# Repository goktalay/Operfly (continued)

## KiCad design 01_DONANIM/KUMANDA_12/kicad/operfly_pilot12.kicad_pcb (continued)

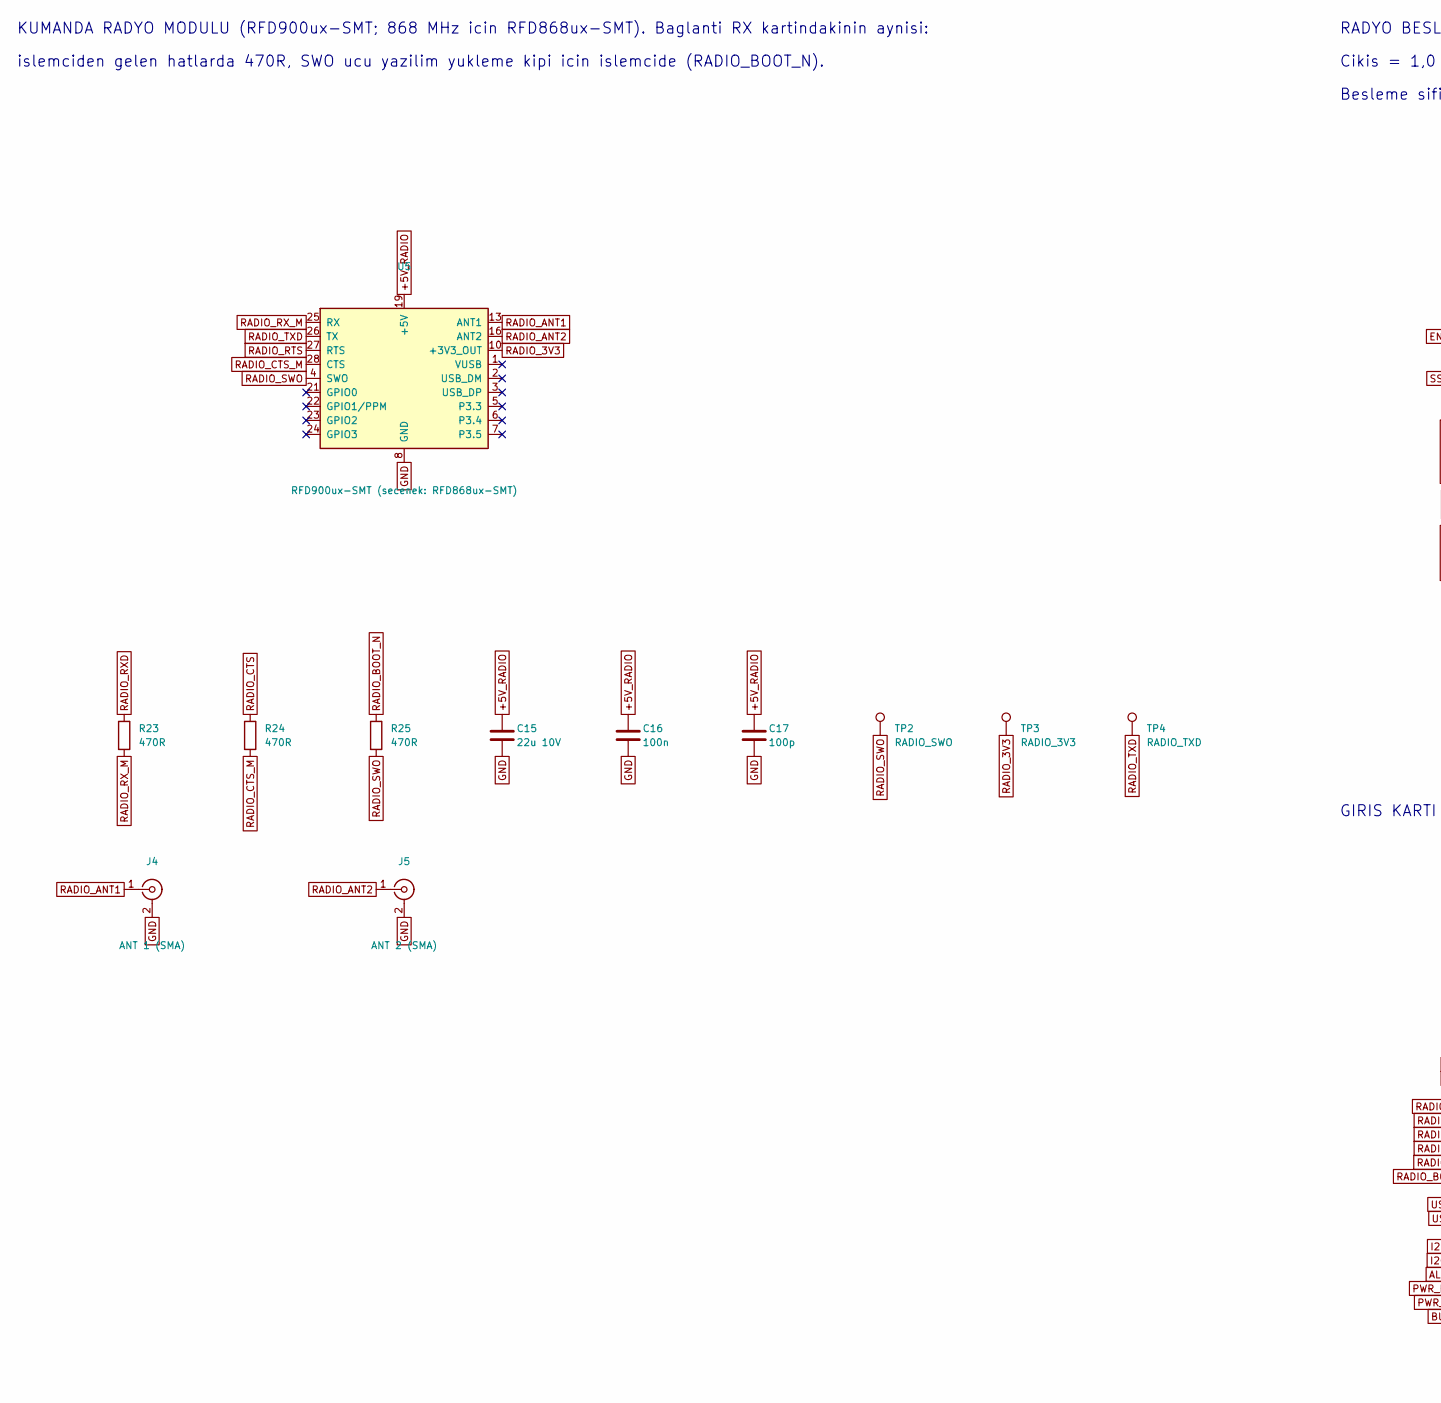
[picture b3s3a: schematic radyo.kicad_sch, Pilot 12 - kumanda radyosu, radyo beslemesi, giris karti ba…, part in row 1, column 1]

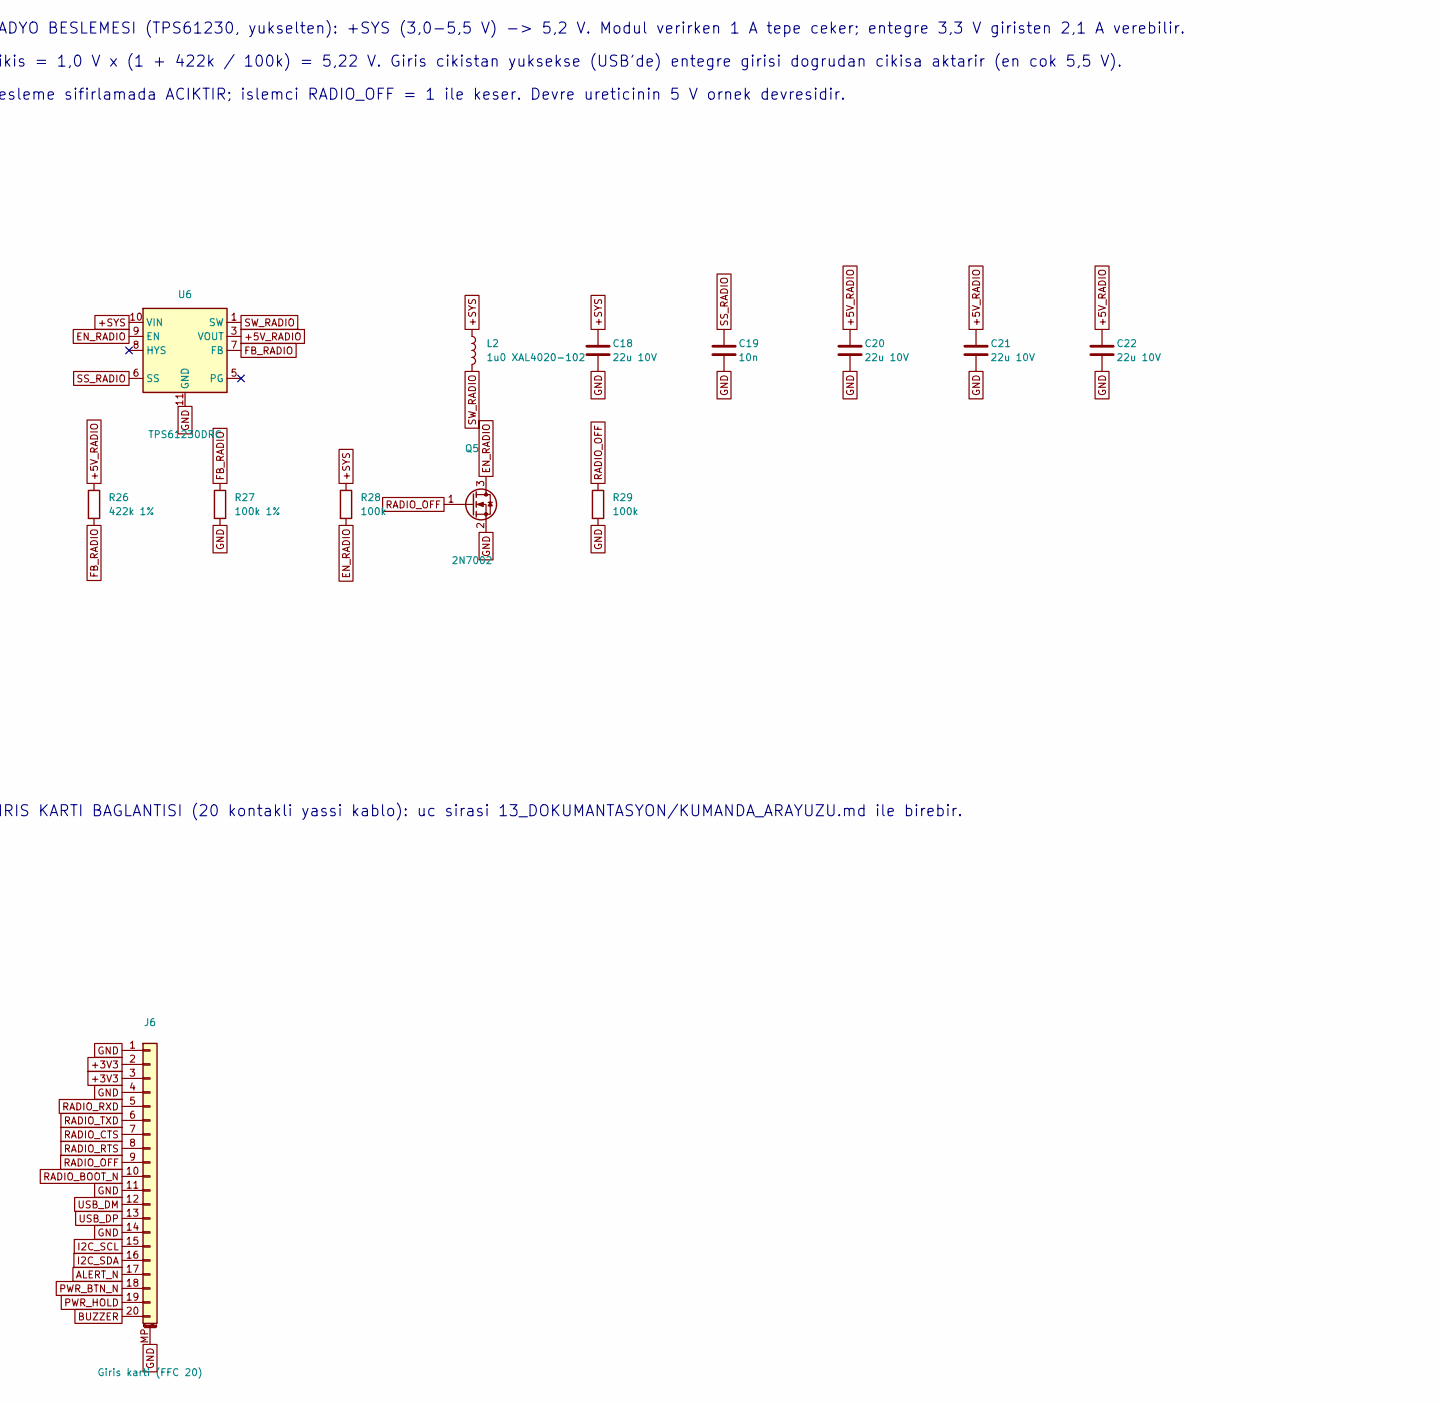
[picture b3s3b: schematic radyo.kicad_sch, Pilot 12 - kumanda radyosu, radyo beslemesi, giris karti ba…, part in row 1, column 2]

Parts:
C15, C18, C20, C21, C22: 22u 10V; C_1206_3216Metric
C16: 100n; C_0402_1005Metric
C17: 100p; C_0402_1005Metric
C19: 10n; C_0402_1005Metric
J4: ANT 1 (SMA); SMA_Amphenol_132289_EdgeMount
J5: ANT 2 (SMA); SMA_Amphenol_132289_EdgeMount
J6: Giris karti (FFC 20); Hirose_FH12-20S-0.5SH_1x20-1MP_P0.50mm_Horizontal
L2: 1u0 XAL4020-102; L_Coilcraft_XAL4020-XXX
Q5: 2N7002; SOT-23
R23, R24, R25: 470R; R_0402_1005Metric
R26: 422k 1%; R_0402_1005Metric
R27: 100k 1%; R_0402_1005Metric
R28, R29: 100k; R_0402_1005Metric
TP2: RADIO_SWO; TestPoint_Pad_D1.0mm
TP3: RADIO_3V3; TestPoint_Pad_D1.0mm
TP4: RADIO_TXD; TestPoint_Pad_D1.0mm
U5: RFD900ux-SMT (secenek: RFD868ux-SMT); RFDesign_RFD900ux-SMT
U6: TPS61230DRC; Texas_S-PVSON-N10_ThermalVias

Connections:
+3V3: J6.2, J6.3; also elsewhere on the board
+5V_RADIO: C15.1, C16.1, C17.1, C20.1, C21.1, C22.1, R26.1, U5.19 (+5V), U6.3 (VOUT), U6.4 (VOUT)
+SYS: C18.1, L2.1, R28.1, U6.10 (VIN); also elsewhere on the board
ALERT_N: J6.17; also elsewhere on the board
BUZZER: J6.20; also elsewhere on the board
EN_RADIO: Q5.3 (D), R28.2, U6.9 (EN)
FB_RADIO: R26.2, R27.1, U6.7 (FB)
GND: C15.2, C16.2, C17.2, C18.2, C19.2, C20.2, C21.2, C22.2, J4.2 (Ext), J5.2 (Ext), J6.1, J6.4, J6.11, J6.14, J6.MP (MountPin), Q5.2 (S), R27.2, R29.2, U5.8 (GND), U5.9 (GND), U5.11 (GND), U5.12 (GND), U5.14 (GND), U5.15 (GND), U5.17 (GND), U5.18 (GND), U5.20 (GND), U5.29 (GND), U5.30 (GND), U6.11 (GND); also elsewhere on the board
I2C_SCL: J6.15; also elsewhere on the board
I2C_SDA: J6.16; also elsewhere on the board
PWR_BTN_N: J6.18; also elsewhere on the board
PWR_HOLD: J6.19; also elsewhere on the board
RADIO_3V3: TP3.1, U5.10 (+3V3_OUT)
RADIO_ANT1: J4.1 (In), U5.13 (ANT1)
RADIO_ANT2: J5.1 (In), U5.16 (ANT2)
RADIO_BOOT_N: J6.10, R25.1
RADIO_CTS: J6.7, R24.1
RADIO_CTS_M: R24.2, U5.28 (CTS)
RADIO_OFF: J6.9, Q5.1 (G), R29.1
RADIO_RTS: J6.8, U5.27 (RTS)
RADIO_RXD: J6.5, R23.1
RADIO_RX_M: R23.2, U5.25 (RX)
RADIO_SWO: R25.2, TP2.1, U5.4 (SWO)
RADIO_TXD: J6.6, TP4.1, U5.26 (TX)
SS_RADIO: C19.1, U6.6 (SS)
SW_RADIO: L2.2, U6.1 (SW), U6.2 (SW)
USB_DM: J6.12; also elsewhere on the board
USB_DP: J6.13; also elsewhere on the board

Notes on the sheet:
KUMANDA RADYO MODULU (RFD900ux-SMT; 868 MHz icin RFD868ux-SMT). Baglanti RX kartindakinin aynisi:
Cikis = 1,0 V x (1 + 422k / 100k) = 5,22 V. Giris cikistan yuksekse (USB'de) entegre girisi dogrudan cikisa aktarir (en cok 5,5 V).
RADYO BESLEMESI (TPS61230, yukselten): +SYS (3,0-5,5 V) -> 5,2 V. Modul verirken 1 A tepe ceker; entegre 3,3 V giristen 2,1 A verebilir.
GIRIS KARTI BAGLANTISI (20 kontakli yassi kablo): uc sirasi 13_DOKUMANTASYON/KUMANDA_ARAYUZU.md ile birebir.
islemciden gelen hatlarda 470R, SWO ucu yazilim yukleme kipi icin islemcide (RADIO_BOOT_N).
Besleme sifirlamada ACIKTIR; islemci RADIO_OFF = 1 ile keser. Devre ureticinin 5 V ornek devresidir.

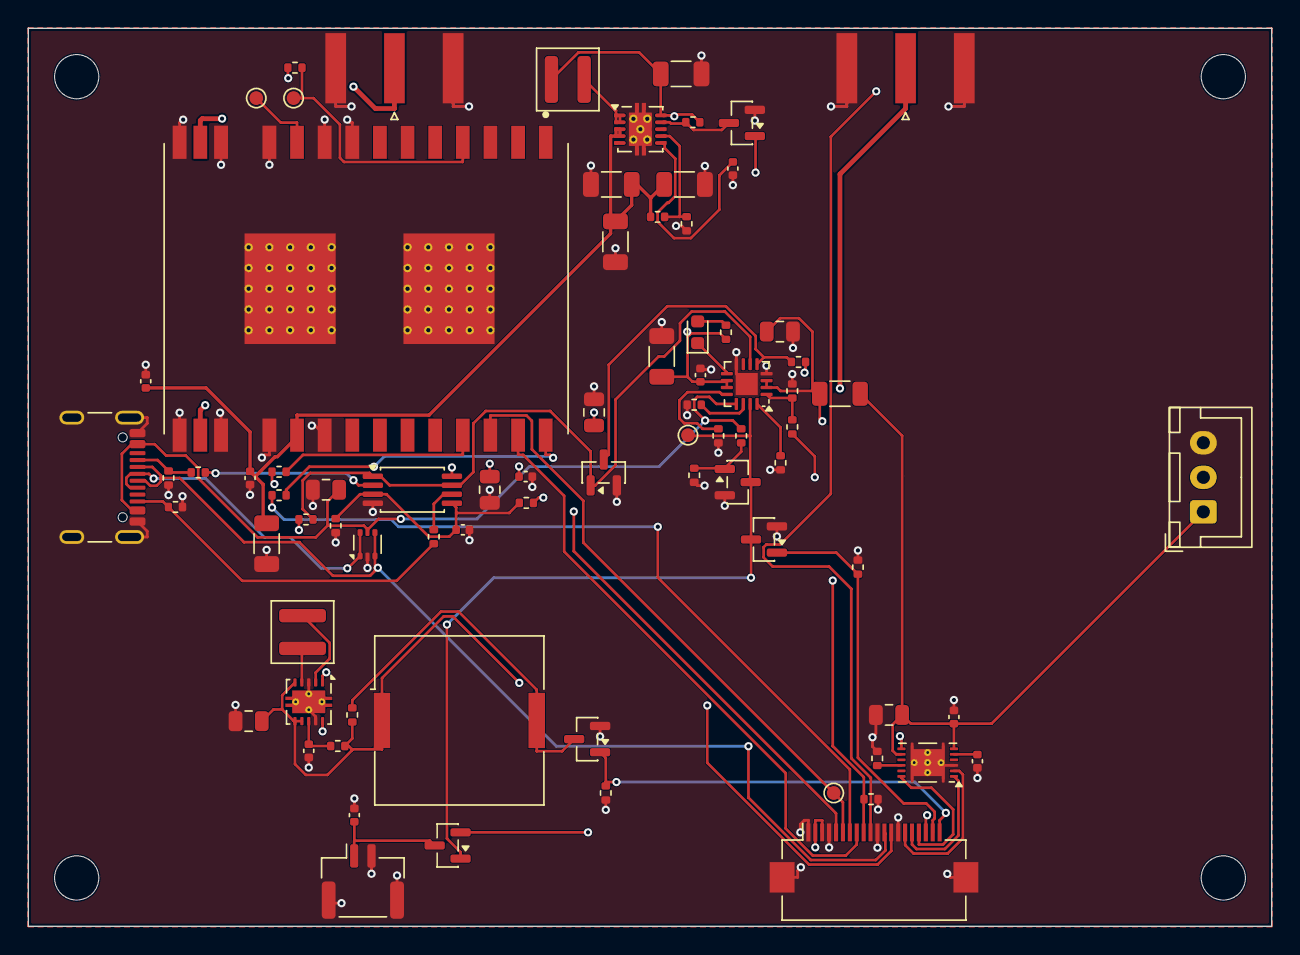
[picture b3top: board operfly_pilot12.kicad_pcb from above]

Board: 4 copper layers, 90.0 x 65.0 mm, 82 parts (0 on the bottom side), 54 nets.

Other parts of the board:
H1, H2, H3, H4: M3; MountingHole_3.2mm_M3

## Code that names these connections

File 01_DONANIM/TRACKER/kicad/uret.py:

"""Operfly Tracker (anten takip birimi) şematiğini üretir.
Çalıştırma: depo kökünden `python 10_ORTAK_ARACLAR/kicad/denetle.py TRACKER operfly_tracker`.

Kaynak bu dosyadır; `*.kicad_sch` çıktıları elle düzenlenmez.
Yapı: düğüm devresi + iki adım motoru sürücüsü (TMC2209-LA: yatay ve dikey eksen) + referans anahtarı girişleri +
isteğe bağlı açı algılayıcı (enkoder) konnektörleri.
Sürücünün uç sırası KiCad kütüphanesindendir; çevre devresi üretilmiş açık kaynaklı bir sürücü kartının şematiğiyle
(aynı entegre, aynı kılıf) karşılaştırılarak çizildi: 5VOUT 4,7 uF, CPI-CPO 22 nF, VCP-VS 100 nF, akım algılama 0,11 ohm,
VREF 2,5 V = 1,77 A RMS. İşlemci pinleri KiCad pin verisindeki alternatif işlevlerle denetlendi.
"""
import os
import sys

KOK = os.path.abspath(os.path.join(os.path.dirname(__file__), "..", "..", ".."))
sys.path.insert(0, os.path.join(KOK, "10_ORTAK_ARACLAR", "kicad"))
from dugum import dugum_sayfasi  # noqa: E402
from kart import C0603, C0805, C1206, ORTAK_URI, Izgara, Kart  # noqa: E402
from sema_uret import Sema, kutuphane_tablolari  # noqa: E402

BURASI = os.path.dirname(os.path.abspath(__file__))
AYAK_URI = "${KIPRJMOD}/../../ORTAK_KUTUPHANE/ayak_izleri/operfly_ayak.pretty"
TANTAL = "Capacitor_Tantalum_SMD:CP_EIA-7343-31_Kemet-D"
R0805 = "Resistor_SMD:R_0805_2012Metric"
k = Kart("operfly_tracker", "2026-11-15")
kok = Sema(k.P, "Operfly Tracker", kagit="A3", tarih=k.T)
kok.metin("Operfly Tracker - anten takip birimi (OPFTRK)", 25.4, 25.4, 3.0)
kok.metin("Sematik betikle uretilir: 01_DONANIM/TRACKER/kicad/uret.py.", 25.4, 33.02, 1.6)

EK = {"PA6": "PAN_STEP", "PA7": "TILT_STEP",              # TIM16_CH1, TIM17_CH1: eksen basina ayri zamanlayici (bagimsiz hiz)
      "PA4": "PAN_DIR", "PA5": "TILT_DIR",
      "PB0": "MOT_EN_N",                                  # 0: suruculer acik (sifirlamada 10k ile kapali)
      "PB6": "TMC_TX", "PB7": "TMC_UART",                 # USART1: iki surucunun tek hatli ayar portu (TX 1k uzerinden ayni hatta)
      "PC6": "PAN_DIAG", "PC7": "TILT_DIAG",              # surucu ariza / yuk algilama cikislari
      "PA0": "PAN_REF", "PA1": "TILT_REF",                # referans anahtarlari (0 = anahtar kapali)
      "PB10": "PAN_SCL", "PB11": "PAN_SDA",               # I2C2: yatay eksen aci algilayicisi (istege bagli)
      "PB3": "TILT_SCL", "PB4": "TILT_SDA"}               # I2C3: dikey eksen aci algilayicisi (istege bagli)
dg = dugum_sayfasi(k, kok, BURASI, ek=EK)

mt = Sema(k.P, "Tracker - motor suruculeri, referans ve aci girisleri", kagit="A1", tarih=k.T, ust=kok, ad="Motor", genel_etiket=True)
kok.alt_sayfa(mt, "motor.kicad_sch", 101.6, 50.8)
mt.metin("ADIM MOTORU SURUCULERI (2 x TMC2209-LA): yatay (PAN) ve dikey (TILT) eksen. Suruculer omurganin korumali 12 V'undan beslenir.", 30, 28)
mt.metin("Cevre devresi uretilmis bir surucu kartindaki gibidir: 5VOUT 4,7 uF, CPI-CPO 22 nF, VCP-VS 100 nF, akim algilama 0,11 ohm.", 30, 34)
mt.metin("Akim: VREF = 5VOUT x 10k / (39k + 10k) = 1,02 V -> faz basina yaklasik 0,7 A RMS (2,5 V = 1,77 A). Yazilim seri porttan dusurebilir.", 30, 40)
mt.metin("Ayar portu tek hattir (iki surucu ayni hatta): adres MS1 ucuyla secilir (PAN = 0, TILT = 1). Islemcinin TX ucu 1k uzerinden hatta baglidir.", 30, 46)
mt.metin("MOT_EN_N sifirlamada 10k ile YUKSEKTIR: islemci acilana kadar motorlara akim verilmez. STDBY, SPREAD ve CLK topraga baglidir.", 30, 52)
VQFN = "Package_DFN_QFN:VQFN-28-1EP_5x5mm_P0.5mm_EP3.7x3.7mm_ThermalVias"
for e, x0, y0, ms1 in (("PAN", 110, 130, "GND"), ("TILT", 110, 330, "+3V3")):
    k.koy(mt, "Driver_Motor:TMC2209-LA", "U", "TMC2209-LA (%s)" % e, x0, y0, {
        "VS": "+12V", "VCC_IO": "+3V3", "GND": "GND", "5VOUT": e + "_5V", "VREF": e + "_VREF", "VCP": e + "_VCP", "CPO": e + "_CPO", "CPI": e + "_CPI",
        "~{EN}": "MOT_EN_N", "STEP": e + "_STEP", "DIR": e + "_DIR", "~{PD}/UART": "TMC_UART", "MS1/AD0": ms1, "MS2/AD1": "GND",
        "SPREAD": "GND", "STDBY": "GND", "CLK": "GND", "DIAG": e + "_DIAG",
        "OA1": e + "_A1", "OA2": e + "_A2", "OB1": e + "_B1", "OB2": e + "_B2", "BRA": e + "_BRA", "BRB": e + "_BRB"}, VQFN)
    g = Izgara(x0 + 70, y0 - 30, sutun=14)
    k.C(mt, g, "100n 50V", "+12V", fp=C0603); k.C(mt, g, "100n 50V", "+12V", fp=C0603); k.C(mt, g, "10u 50V", "+12V", fp=C1206)
    k.C(mt, g, "100u 25V", "+12V", fp=TANTAL)
    k.C(mt, g, "100n 50V", e + "_VCP", "+12V", fp=C0603); k.C(mt, g, "22n 50V", e + "_CPO", e + "_CPI", fp=C0603)
    k.C(mt, g, "4u7 10V", e + "_5V", fp=C0805); k.C(mt, g, "100n", "+3V3")
    k.R(mt, g, "39k 1%", e + "_5V", e + "_VREF"); k.R(mt, g, "10k 1%", e + "_VREF", "GND"); k.C(mt, g, "100n", e + "_VREF")
    k.R(mt, g, "0R11 1% 0,5 W", e + "_BRA", "GND", fp=R0805); k.R(mt, g, "0R11 1% 0,5 W", e + "_BRB", "GND", fp=R0805)
    g.satir()
    k.parca(mt, g, "Connector_Generic:Conn_01x04", "J", "Motor %s (JST-XH: A1, A2, B1, B2)" % e,
            {"Pin_1": e + "_A1", "Pin_2": e + "_A2", "Pin_3": e + "_B1", "Pin_4": e + "_B2"}, "Connector_JST:JST_XH_B4B-XH-A_1x04_P2.50mm_Vertical", bosluk=1, dx=8)
    k.olcum_noktasi(mt, g, e + "_DIAG"); k.olcum_noktasi(mt, g, e + "_VREF")

mt.metin("ORTAK HATLAR: surucu acma ucu ve ayar portu.", 520, 80)
g = Izgara(540, 115, sutun=10)
k.R(mt, g, "10k", "+3V3", "MOT_EN_N"); k.R(mt, g, "1k", "TMC_TX", "TMC_UART"); k.R(mt, g, "100k", "+3V3", "TMC_UART")
k.olcum_noktasi(mt, g, "TMC_UART"); k.olcum_noktasi(mt, g, "MOT_EN_N")

mt.metin("REFERANS ANAHTARLARI (JST-GH 3: +3V3, sinyal, GND): acilista her eksen bilinen bir noktaya gider. Mekanik ya da Hall/optik anahtar olabilir.", 520, 180)
mt.metin("Giris 10k ile yukari cekili, 1k + 100 nF suzgecli; anahtar kapaninca 0 okunur.", 520, 186)
g = Izgara(540, 225, sutun=12)
for e in ("PAN", "TILT"):
    k.parca(mt, g, "Connector_Generic_MountingPin:Conn_01x03_MountingPin", "J", "Referans %s" % e,
            {"Pin_1": "+3V3", "Pin_2": e + "_REF_K", "Pin_3": "GND", "MountPin": "GND"}, "Connector_JST:JST_GH_SM03B-GHS-TB_1x03-1MP_P1.25mm_Horizontal", bosluk=1, dx=8)
    k.R(mt, g, "10k", "+3V3", e + "_REF_K"); k.R(mt, g, "1k", e + "_REF_K", e + "_REF"); k.C(mt, g, "100n", e + "_REF")

mt.metin("ACI ALGILAYICI KONNEKTORLERI (istege bagli; JST-GH 4: +3V3, GND, SCL, SDA): mil ucundaki miknatisli aci algilayicilar icin, eksen basina", 520, 290)
mt.metin("ayri I2C hatti (ayni adresli iki algilayici kullanilabilsin diye). Adim kacirmayi yakalar; ruzgarli yerde onerilir.", 520, 296)
g = Izgara(540, 335, sutun=12)
for e in ("PAN", "TILT"):
    k.parca(mt, g, "Connector_Generic_MountingPin:Conn_01x04_MountingPin", "J", "Aci algilayici %s" % e,
            {"Pin_1": "+3V3", "Pin_2": "GND", "Pin_3": e + "_SCL", "Pin_4": e + "_SDA", "MountPin": "GND"},
            "Connector_JST:JST_GH_SM04B-GHS-TB_1x04-1MP_P1.25mm_Horizontal", bosluk=1, dx=8)
    k.R(mt, g, "2k2", "+3V3", e + "_SCL"); k.R(mt, g, "2k2", "+3V3", e + "_SDA")
mt.yaz(os.path.join(BURASI, "motor.kicad_sch"))

kok.yaz(os.path.join(BURASI, "operfly_tracker.kicad_sch"))
kutuphane_tablolari(BURASI, [kok, dg, mt], {"operfly": ORTAK_URI, "operfly_ayak": AYAK_URI})
print("yazildi: operfly_tracker (kok + 2 sayfa)")

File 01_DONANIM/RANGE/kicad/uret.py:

"""Operfly Range 10 / 30 / 100 şematiğini üretir. Çalıştırma: depo kökünden `python 10_ORTAK_ARACLAR/kicad/denetle.py RANGE operfly_range`.

Kaynak bu dosyadır; `*.kicad_sch` çıktıları elle düzenlenmez.
Üç ürün tek karttır: düğüm devresi + hazır lazer mesafe modülü için arayüz (5 V anahtarlı besleme, 3,3 V seri port, I2C).
Menzili takılan modül belirler. Arayüz değerleri aday modüllerin veri sayfalarına göredir: besleme 5 V, haberleşme 3,3 V seviyeli
(Benewake TFmini Plus 12 m, TF02-Pro 40 m, TF03-100 100 m).
"""
import os
import sys

KOK = os.path.abspath(os.path.join(os.path.dirname(__file__), "..", "..", ".."))
sys.path.insert(0, os.path.join(KOK, "10_ORTAK_ARACLAR", "kicad"))
from dugum import dugum_sayfasi  # noqa: E402
from kart import C0805, C1206, ORTAK_URI, Izgara, Kart  # noqa: E402
from sema_uret import Sema, kutuphane_tablolari  # noqa: E402

BURASI = os.path.dirname(os.path.abspath(__file__))
k = Kart("operfly_range", "2026-11-15")
kok = Sema(k.P, "Operfly Range", kagit="A3", tarih=k.T)
kok.metin("Operfly Range 10 / 30 / 100 - mesafe sensoru karti (OPFR10, OPFR30, OPFR1H)", 25.4, 25.4, 3.0)
kok.metin("Sematik betikle uretilir: 01_DONANIM/RANGE/kicad/uret.py. Uc urun ayni karttir; menzili takilan modul belirler.", 25.4, 33.02, 1.6)

EK = {"PA2": "SENS_TX", "PA3": "SENS_RX",          # USART2: modulun seri portu (3,3 V)
      "PB10": "SENS_SCL_M", "PB11": "SENS_SDA_M",  # I2C2: I2C ile calisan moduller icin (ayni zamanda modulun G/C ucu)
      "PA4": "SENS_PWR_EN",                        # 1: module 5 V ver (sifirlamada kapali)
      "PA0": "SENS_VSENS"}                         # ADC1_IN0: modul besleme gerilimi / 2
dg = dugum_sayfasi(k, kok, BURASI, ek=EK)

sn = Sema(k.P, "Operfly Range - mesafe modulu arayuzu", kagit="A3", tarih=k.T, ust=kok, ad="Sensor", genel_etiket=True)
kok.alt_sayfa(sn, "sensor.kicad_sch", 101.6, 50.8)
sn.metin("MODUL KONNEKTORU (JST-GH 6, Operfly tanimi): 1 +5 V, 2 GND, 3 kart -> modul (modulun RX'i), 4 modul -> kart (modulun TX'i), 5 SCL / G-C, 6 SDA.", 20, 22)
sn.metin("Modulun kendi kablosu bu siraya gore hazirlanir. Hatlar 3,3 V seviyelidir; 470R seri direncler ve koruma diyotu kablo tarafindadir.", 20, 28)
g = Izgara(40, 70, sutun=11)
k.parca(sn, g, "Connector_Generic_MountingPin:Conn_01x06_MountingPin", "J", "Mesafe modulu", {"Pin_1": "+5V_SENS", "Pin_2": "GND", "Pin_3": "SENS_RXD", "Pin_4": "SENS_TXD",
        "Pin_5": "SENS_SCL", "Pin_6": "SENS_SDA", "MountPin": "GND"}, "Connector_JST:JST_GH_SM06B-GHS-TB_1x06-1MP_P1.25mm_Horizontal", dx=8)
k.R(sn, g, "470R", "SENS_TX", "SENS_RXD"); k.R(sn, g, "470R", "SENS_TXD", "SENS_RX"); k.R(sn, g, "100k", "+3V3", "SENS_RX")
x, y = g.yer(); g.yer()
k.koy(sn, "Power_Protection:USBLC6-2P6", "D", "USBLC6-2P6", x + 10, y, {"1": "SENS_RXD", "6": "SENS_RXD", "3": "SENS_TXD", "4": "SENS_TXD", "5": "+3V3", "2": "GND"}, "Package_TO_SOT_SMD:SOT-666")
k.R(sn, g, "100R", "SENS_SCL_M", "SENS_SCL"); k.R(sn, g, "100R", "SENS_SDA_M", "SENS_SDA")
k.R(sn, g, "2k2", "+3V3", "SENS_SCL_M"); k.R(sn, g, "2k2", "+3V3", "SENS_SDA_M")

sn.metin("MODUL BESLEMESI: 5 V, P kanal MOSFET ile anahtarli (islemci modulu kapatip acabilir), 0,5 A tutma akimli kendini onaran sigorta.", 20, 125)
sn.metin("Aday moduller ortalama 0,11-0,2 A, tepe 0,3 A ceker. Kapi kondansatoru acilisi yumusatir. SENS_VSENS = besleme / 2.", 20, 131)
g = Izgara(40, 170, sutun=11)
x, y = g.yer()
k.koy(sn, "Transistor_FET:DMP3099L", "Q", "DMP3099L", x, y, {"S": "+5V", "D": "SENS_5V_SW", "G": "SENS_GATE"}, "Package_TO_SOT_SMD:SOT-23")
k.R(sn, g, "100k", "+5V", "SENS_GATE"); k.C(sn, g, "100n", "+5V", "SENS_GATE")
x, y = g.yer()
k.koy(sn, "Transistor_FET:2N7002", "Q", "2N7002", x, y, {"D": "SENS_GATE_R", "S": "GND", "G": "SENS_PWR_EN"}, "Package_TO_SOT_SMD:SOT-23")
k.R(sn, g, "10k", "SENS_GATE", "SENS_GATE_R"); k.R(sn, g, "100k", "SENS_PWR_EN", "GND")
k.iki(sn, g, "Device:Polyfuse", "F", "0,5 A tutma (1206)", "SENS_5V_SW", "+5V_SENS", "Fuse:Fuse_1206_3216Metric")
k.C(sn, g, "47u 10V", "+5V_SENS", fp=C1206); k.C(sn, g, "100n", "+5V_SENS")
k.R(sn, g, "10k 1%", "+5V_SENS", "SENS_VSENS"); k.R(sn, g, "10k 1%", "SENS_VSENS", "GND"); k.C(sn, g, "100n", "SENS_VSENS")
k.olcum_noktasi(sn, g, "+5V_SENS")
sn.yaz(os.path.join(BURASI, "sensor.kicad_sch"))

kok.yaz(os.path.join(BURASI, "operfly_range.kicad_sch"))
kutuphane_tablolari(BURASI, [kok, dg, sn], {"operfly": ORTAK_URI})
print("yazildi: operfly_range (kok + 2 sayfa)")
